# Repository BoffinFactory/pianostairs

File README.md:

## pianostairs

###Dependencies

####Programs
* lilypond (For generating sound files)
* timidity (For generating sound files)
* python

####Python modules
* Tkinter
* Scrolled Text
* PIL
* pygame

###Building
$ make  
It'll generate the necessary sound files in ./sounds/

If python doesn't live at /usr/bin/python, adjust the shebang in main.py

###Running
$ ./main.py

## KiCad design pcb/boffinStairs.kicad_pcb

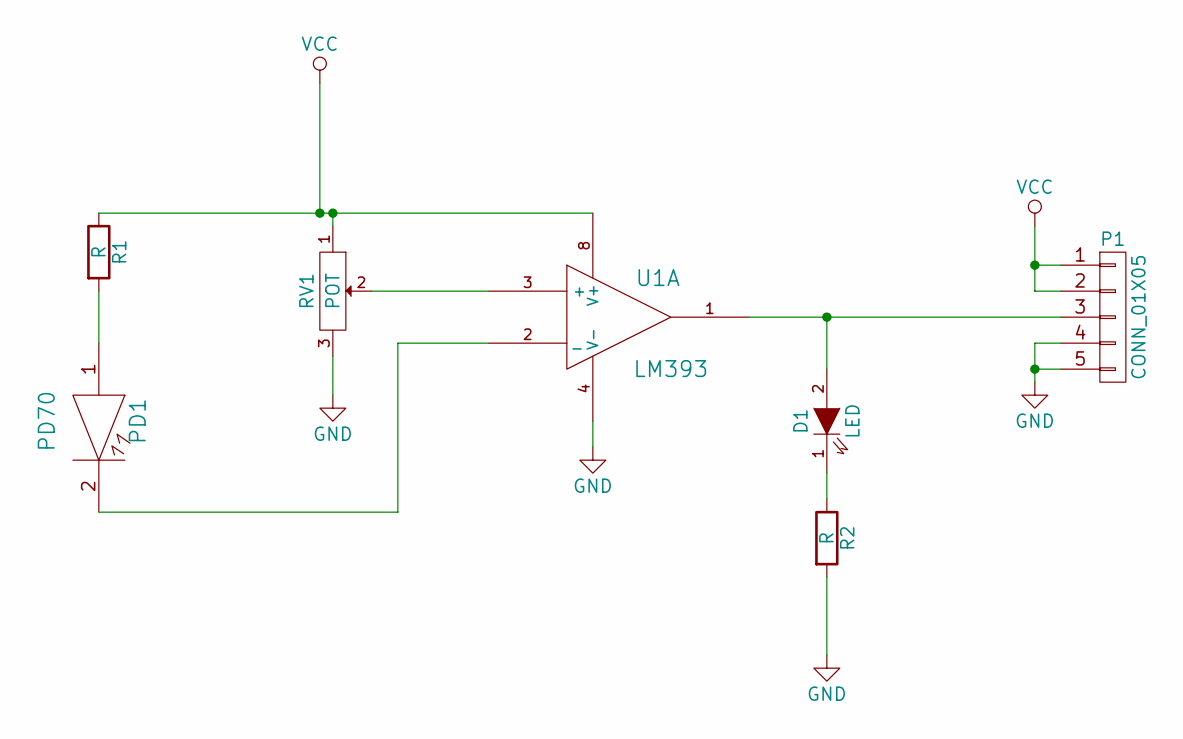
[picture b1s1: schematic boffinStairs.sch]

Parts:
D1: LED; LED_0805
P1: CONN_01X05; Socket_Strip_Straight_1x05
PD1: PD70
R1, R2: R; R_0805
RV1: POT; TC33
U1: LM393; TSSOP8

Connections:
GND: P1.4, P1.5, R2.2, RV1.3, U1.4 (V-)
unnamed: D1.1 (K), R2.1
unnamed: D1.2 (A), P1.3, U1.1
unnamed: PD1.1, R1.2
unnamed: PD1.2, U1.2 (_)
unnamed: RV1.2, U1.3 (+)
VCC: P1.1, P1.2, R1.1, RV1.1, U1.8 (V+)

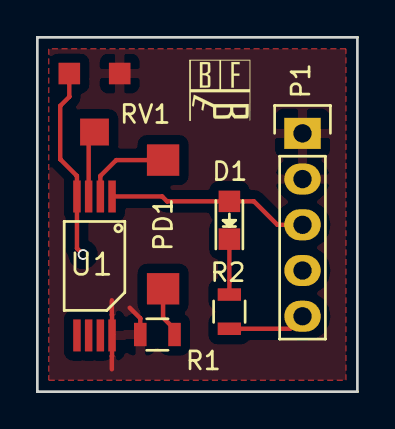
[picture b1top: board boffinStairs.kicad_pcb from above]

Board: 2 copper layers, 17.8 x 19.7 mm, 7 parts (0 on the bottom side), 7 nets.

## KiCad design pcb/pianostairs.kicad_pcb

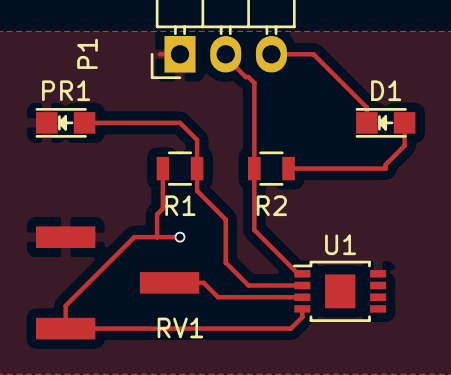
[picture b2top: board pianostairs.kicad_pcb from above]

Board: 2 copper layers, 7 parts (0 on the bottom side), 6 nets.

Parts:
D1: LED; LED-0805
P1: CONN_01X03; Pin_Header_Angled_1x03
PR1: Photores; LED-0805
R1, R2: R; R_0805
RV1: POT; 3361P Bourns trimming Potentiometer
U1: LM393; MSOP-8-1EP_3x3mm_Pitch0.65mm

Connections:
+5V: P1.1, PR1.1, RV1.1, U1.8
Earth: D1.1, P1.3, R1.2, RV1.3, U1.4
unnamed: D1.2, R2.1
unnamed: PR1.2, R1.1, U1.2
unnamed: P1.2, R2.2, U1.1
unnamed: RV1.2, U1.3

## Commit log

2015-11-13 init
2015-11-19 initial framework for player.py. set_key works
2015-11-21 start of pcb design new file: pcb/3361P-104GLFCT-ND.pretty/3361P Bourns trimming Potentiometer.kicad_mod new file: pcb/fp-lib-table new file: pcb/pianostairs-cache.lib new file: pcb/pianostairs.bak n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
2015-11-21 moved audio files
2015-11-21 deleted: Piano.ff.Gb1.aiff deleted: Piano.mf.G2.aiff
2015-11-21 renamed: _readme_and_license.txt -> audio/_readme_and_license.txt
2015-11-21 new file: pianostairs/pianostairs.ino
2015-11-23 restructured some stuff
2015-11-24 added gui.py
2015-11-26 added makefile for generating sound files
2015-12-01 added keyboard image. central note highlighted when key selected
2015-12-01 fixed the "async handler deleted by the wrong thread" bug
2015-12-02 BUGFIX: The wrong C was being included in some keys, since the octave switch is at C and not A. Added draw_keyboard and related functions
2015-12-03 keyboard works
2015-12-03 BUGFIX: misinterpreted relative tone syntax in lilypad. fixed.
2015-12-03 found workaround for python's brain-damaged lack of proper linkage specifiers
2015-12-10 restructured the "python doesn't have proper linkage specifiers" kludge
2015-12-10 added parser, copeland, demo button
2015-12-10 added trombone and tuba parts to copeland.score around measures 25-27
2015-12-10 added volume control
2015-12-10 gui keyboard now reflects what the stairs are doing
2015-12-18 demo now resets the gui when it finishes
2015-12-18 keyboard resizes along with window now. fullscreen now default
2016-01-05 more feedback when changing key. integrated key change into demo
2016-01-05 added a few instruments. makefile no longer generates notes below A0 or above Db8
2016-01-12 integrated decoder into main.py
2016-01-14 tested with hardware. works
2016-01-22 added initial framework for challenge mode
2016-02-11 new file: PD70.pretty/PD70.kicad_mod new file: PD70.pretty/TC33.kicad_mod new file: PD70.pretty/TSSOP8.kicad_mod new file: boffinStairs-cache.lib new file: boffinStairs.bak new file: boffinStairs.kic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
2016-02-11 new file: boffinStairs-B.Cu.gbr new file: boffinStairs-B.SilkS.gbr new file: boffinStairs-Edge.Cuts.gbr new file: boffinStairs-F.Cu.gbr new file: boffinStairs-F.SilkS.gbr new file: boffinStairs-botto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
2016-02-11 modified: boffinStairs-B.Cu.gbr new file: boffinStairs-B.Mask.gbr modified: boffinStairs-B.SilkS.gbr modified: boffinStairs-Edge.Cuts.gbr modified: boffinStairs-F.Cu.gbr new file: boffinStairs-F.Mask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
2016-02-11 new file: bf.kicad_mod modified: boffinStairs-B.Cu.gbr modified: boffinStairs-B.Mask.gbr modified: boffinStairs-B.SilkS.gbr modified: boffinStairs-Edge.Cuts.gbr modified: boffinStairs-F.Cu.gbr modifi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
2016-08-31 refactored gui code a bit
